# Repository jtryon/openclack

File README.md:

# OpenClack.TKL

## Preface
This repository contains all the source files needed to create a 87 key (tenkeyless) mechanical keyboard.</br>
In order to actually build this keep in mind you'll need access to the following.
* PCB fabrication.
* CNC, laser or waterjet cutting.
* Soldering iron and supplies.
* A source for your switches, stabilizers and electronic components.

## Licensing
Software in this project is licensed under the GPL.  See GPL.md</br>
Hardware in this project is licensed under the TAPR.  See TAPR.md

## Details
* Tenkeyless layout.
* Compatible with Cherry MX switches and both Cherry and Costar stabilizers.
* LED support for each key.
* Does not require a resistor for each LED.
* N-Key roll-over, no ghosting, 1 diode per switch.
* Firmware which allows for custom key mapping, macros, de-bouncing and LED control.
* Mini-B connector.
* Teensy 2.0++ controller.
Some images of a completed prototype based on the designs in this repo are in the "prototype_images" folder.

## Project Files
* /dashkey/* - Firmware for the keyboard, codenamed DashKey.  Coded by SiberX.
* /fabrication/* - Final project files to be sent off and fabricated.
* /kicad_files/* - Kicad project.  Open the file "openclack-tkl.pro".
* /notes/* - Notes explaining the LED configuration, parts list, info on the boost converter, resistors.
* openclack.skp - Rough 3D render of the project (SketchUp).

## Instructions
There's currently no guide on how to do this but if you're technically inclined it should be doable with all the files contained herein.  If someone wants to develop a guide feel free to contribute!

## Loading Firmware
WIP

## Sources/Thanks
Thanks to the folks at http://deskthority.net/ for helping out when I had questions about measurements!</br>
Also a big thanks to BathroomEpiphanies.  Wouldn't have been able to do it without your amazing wiki.  [Check it out here!](http://deskthority.net/wiki/KiCAD_keyboard_PCB_design_guide)

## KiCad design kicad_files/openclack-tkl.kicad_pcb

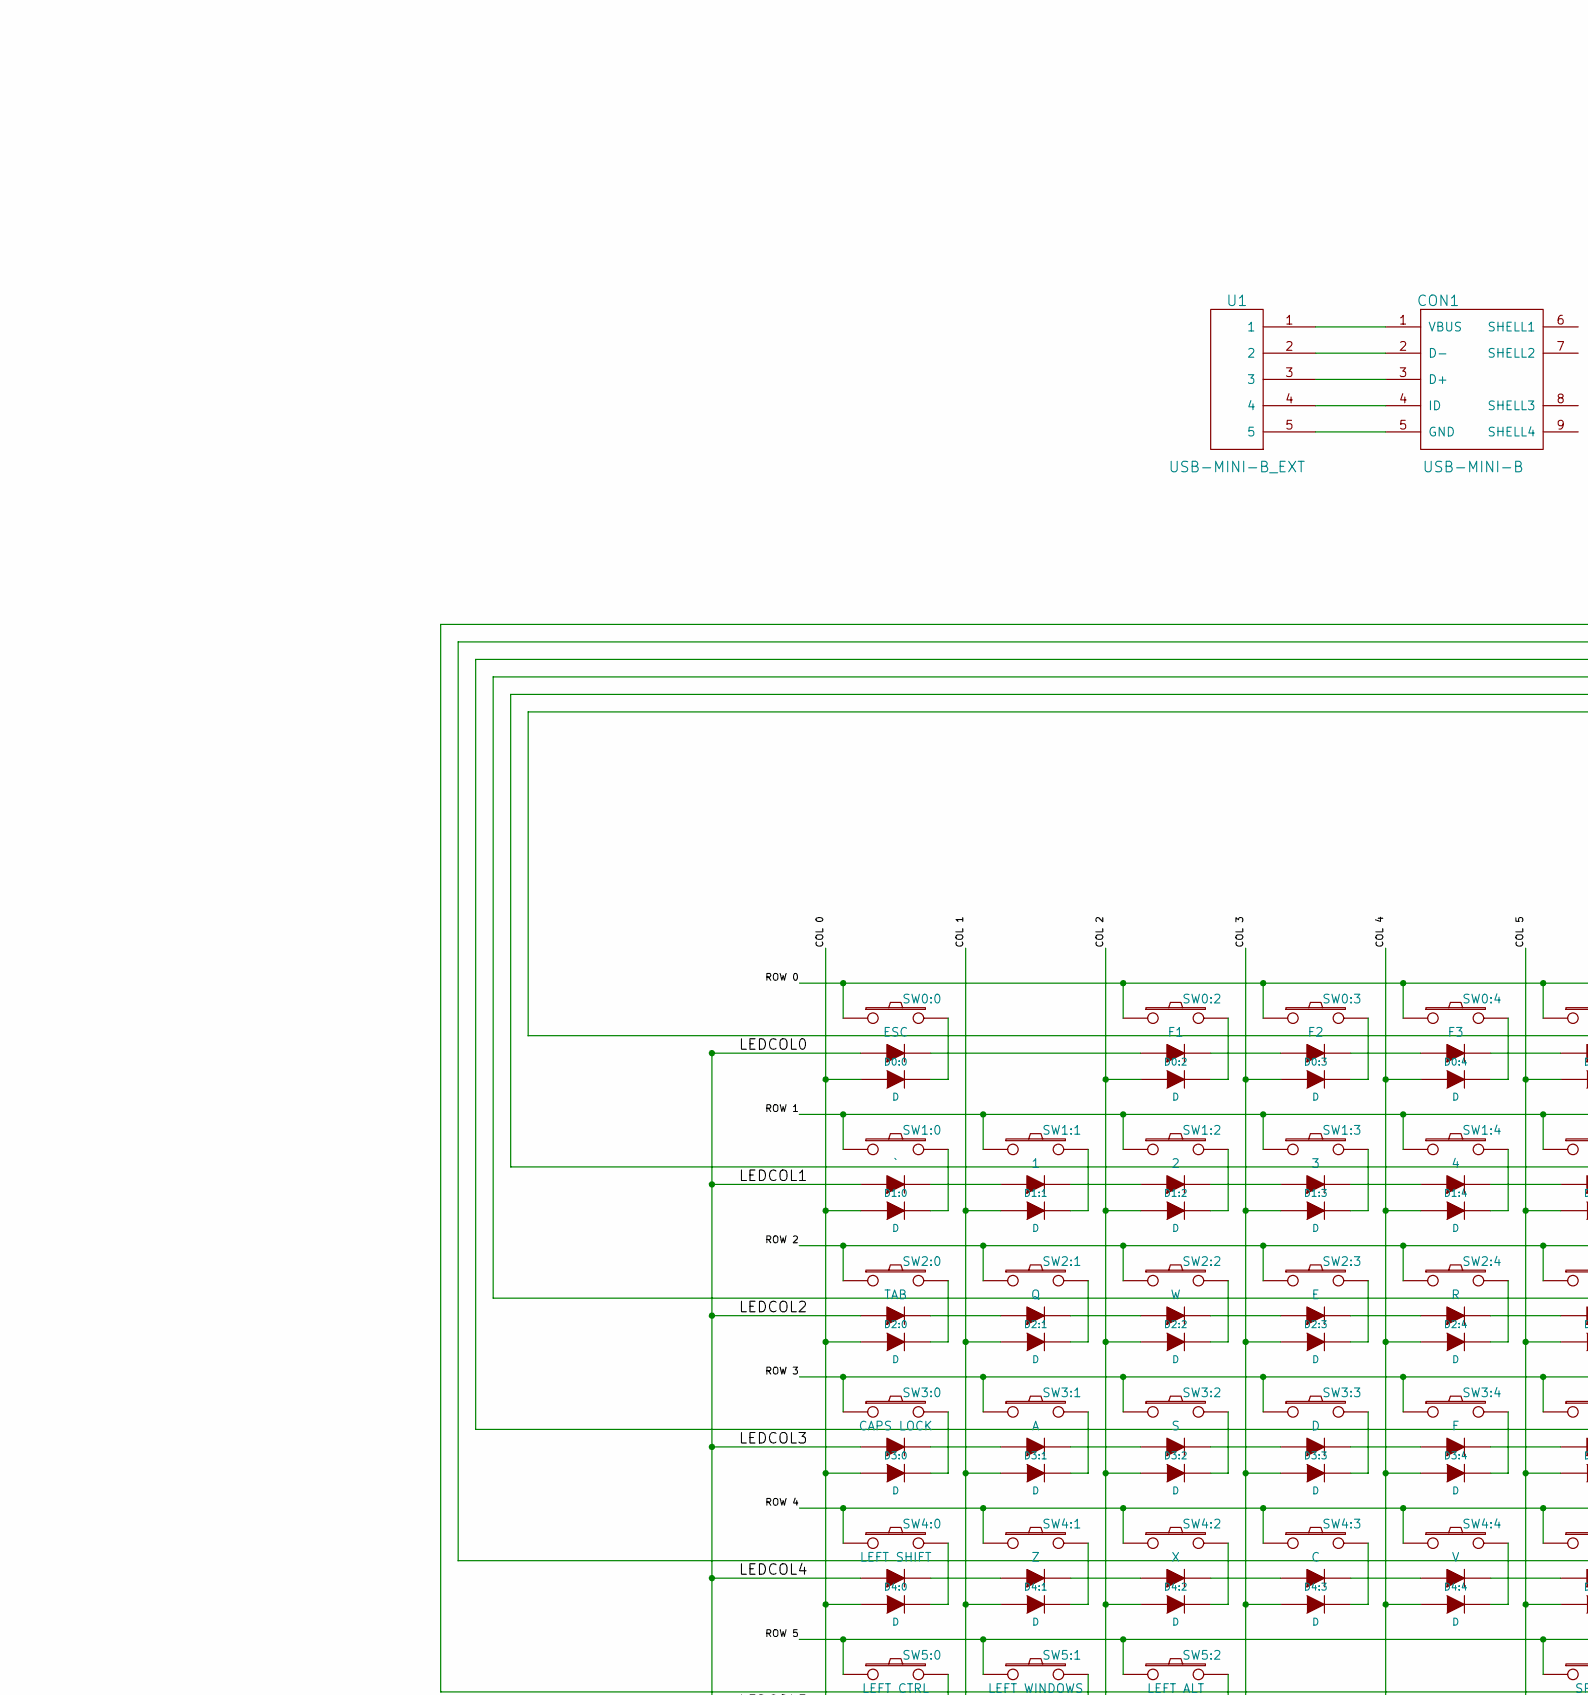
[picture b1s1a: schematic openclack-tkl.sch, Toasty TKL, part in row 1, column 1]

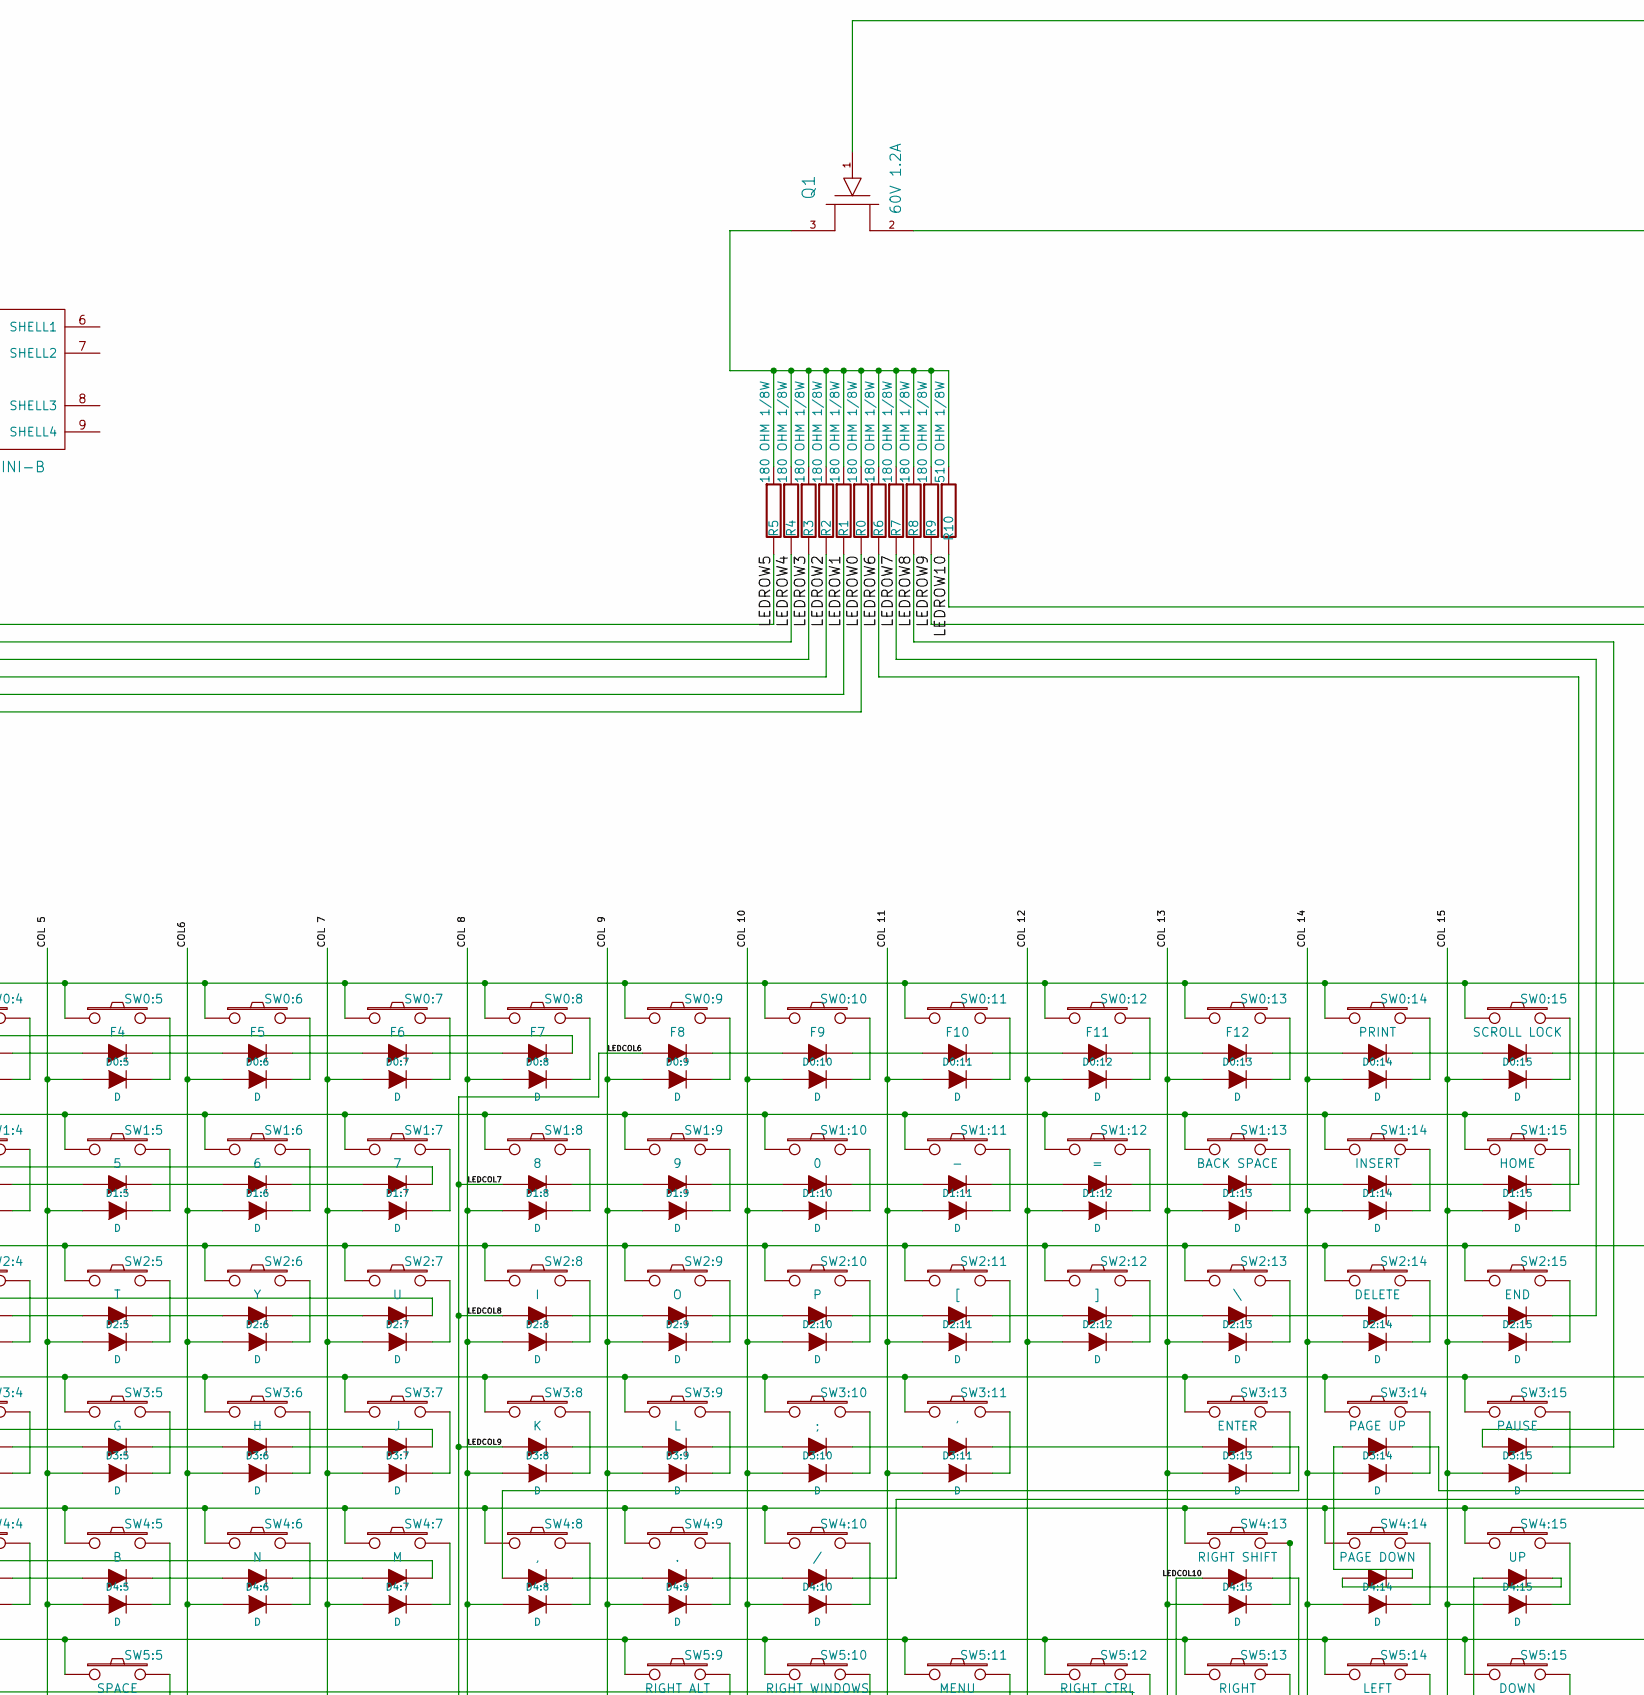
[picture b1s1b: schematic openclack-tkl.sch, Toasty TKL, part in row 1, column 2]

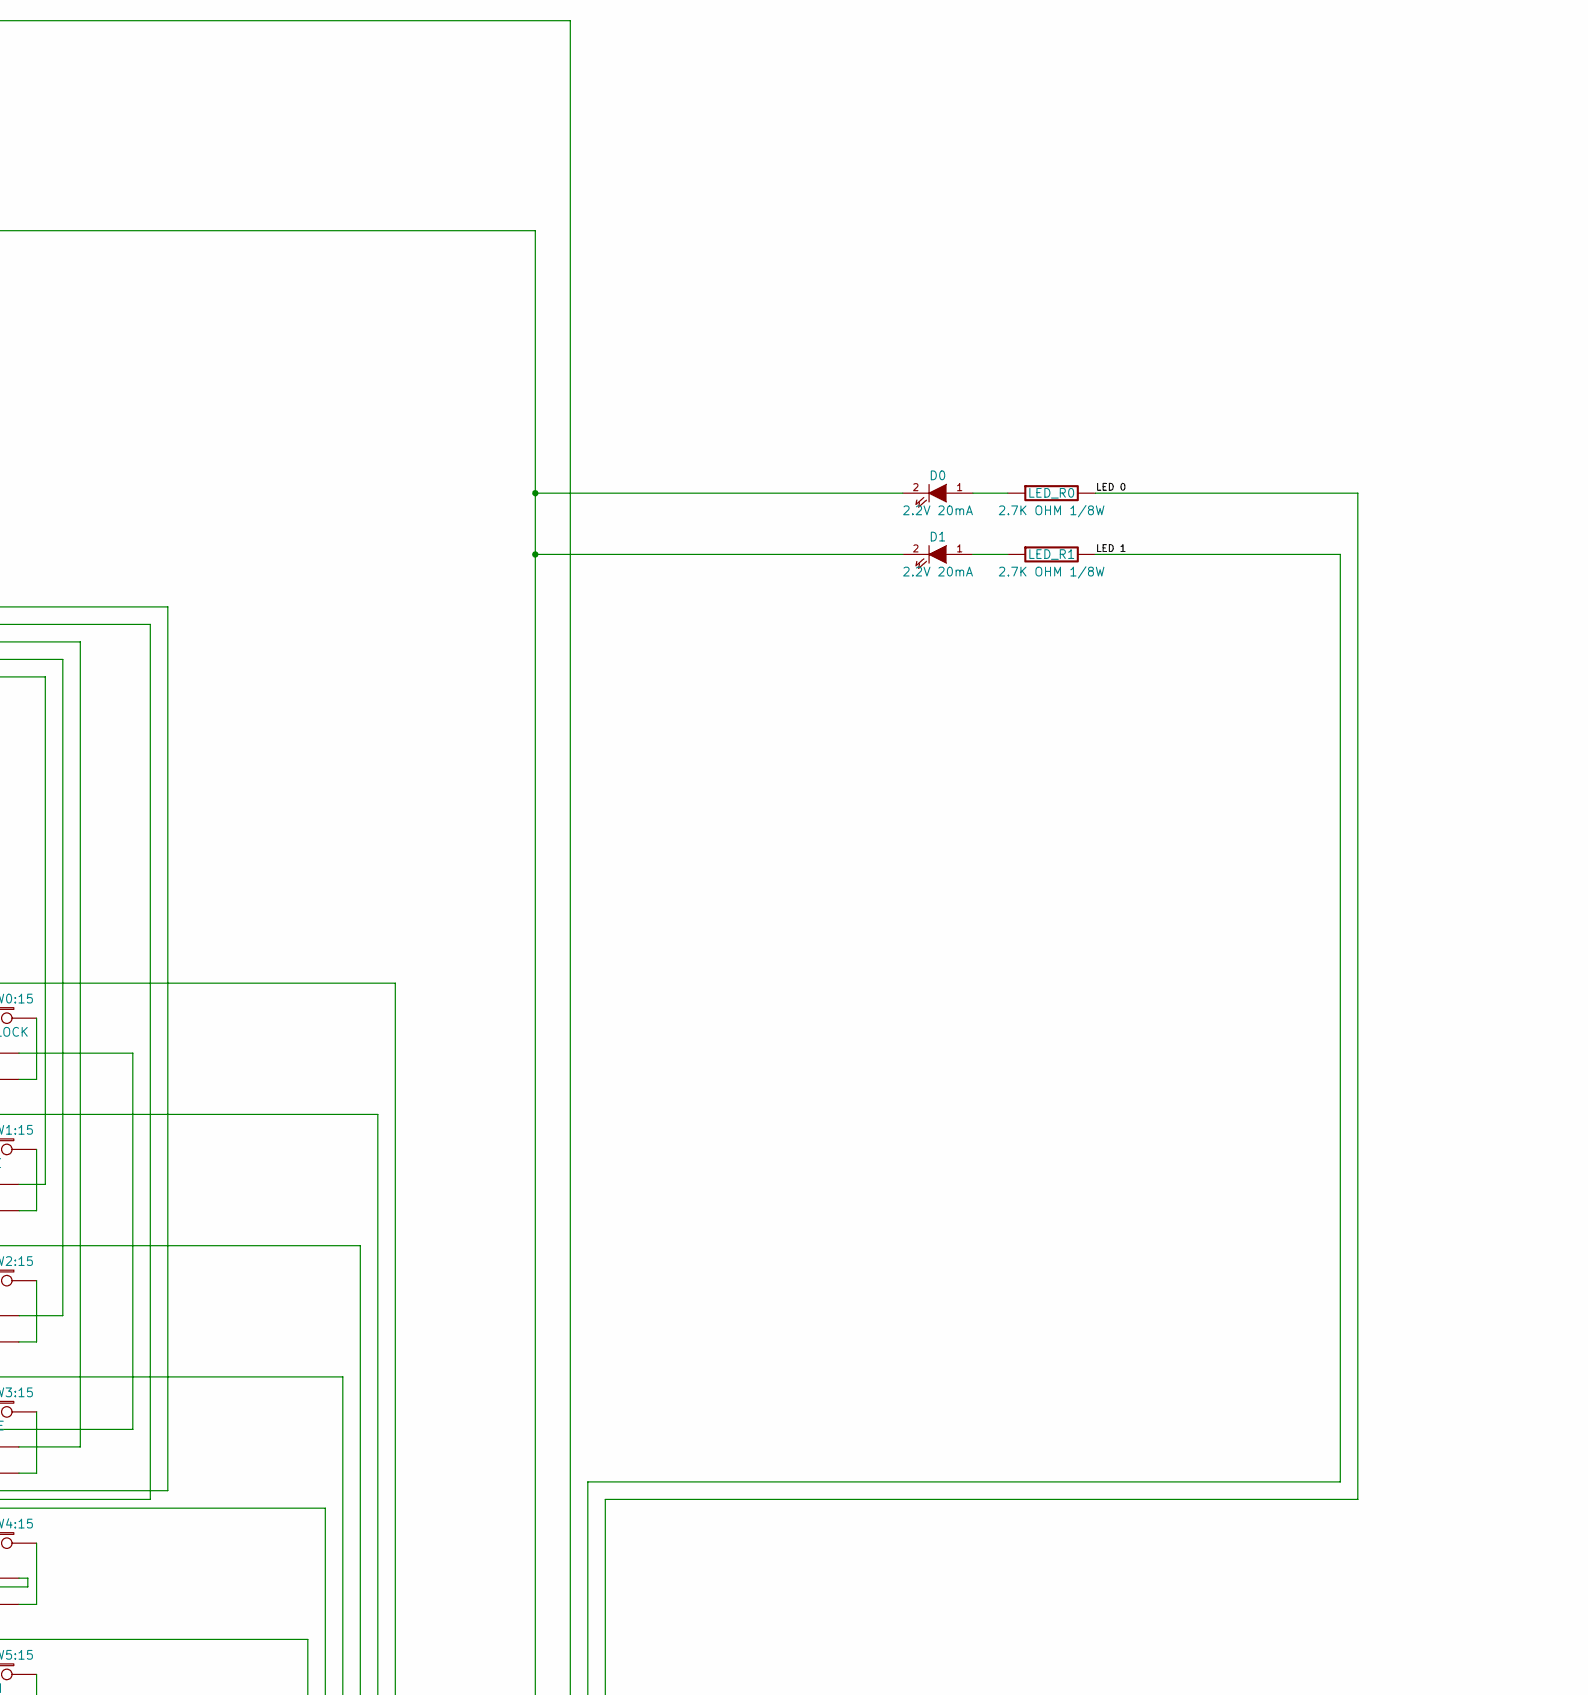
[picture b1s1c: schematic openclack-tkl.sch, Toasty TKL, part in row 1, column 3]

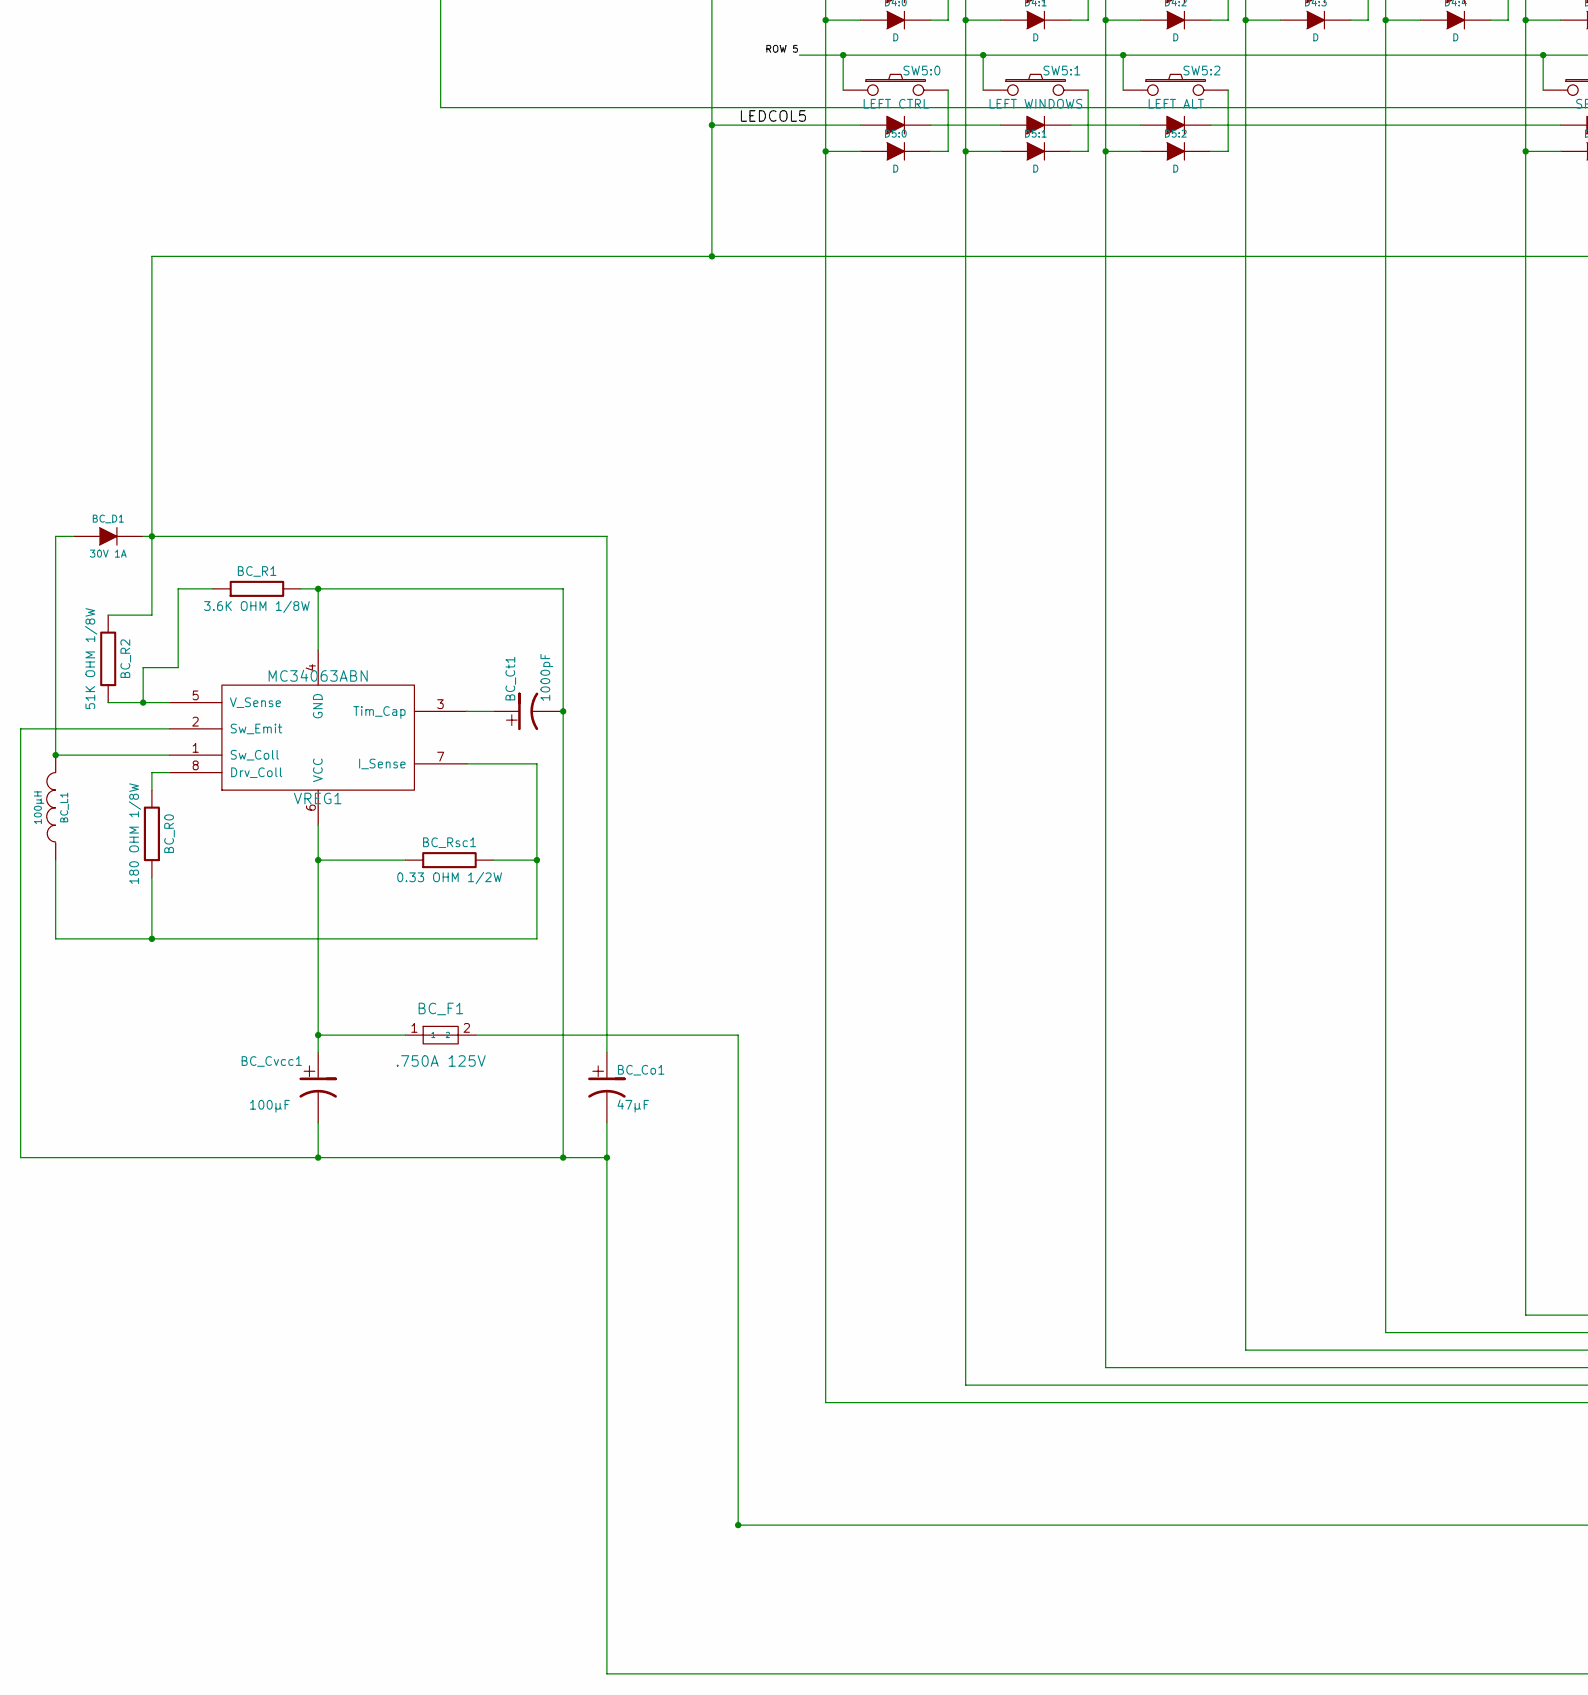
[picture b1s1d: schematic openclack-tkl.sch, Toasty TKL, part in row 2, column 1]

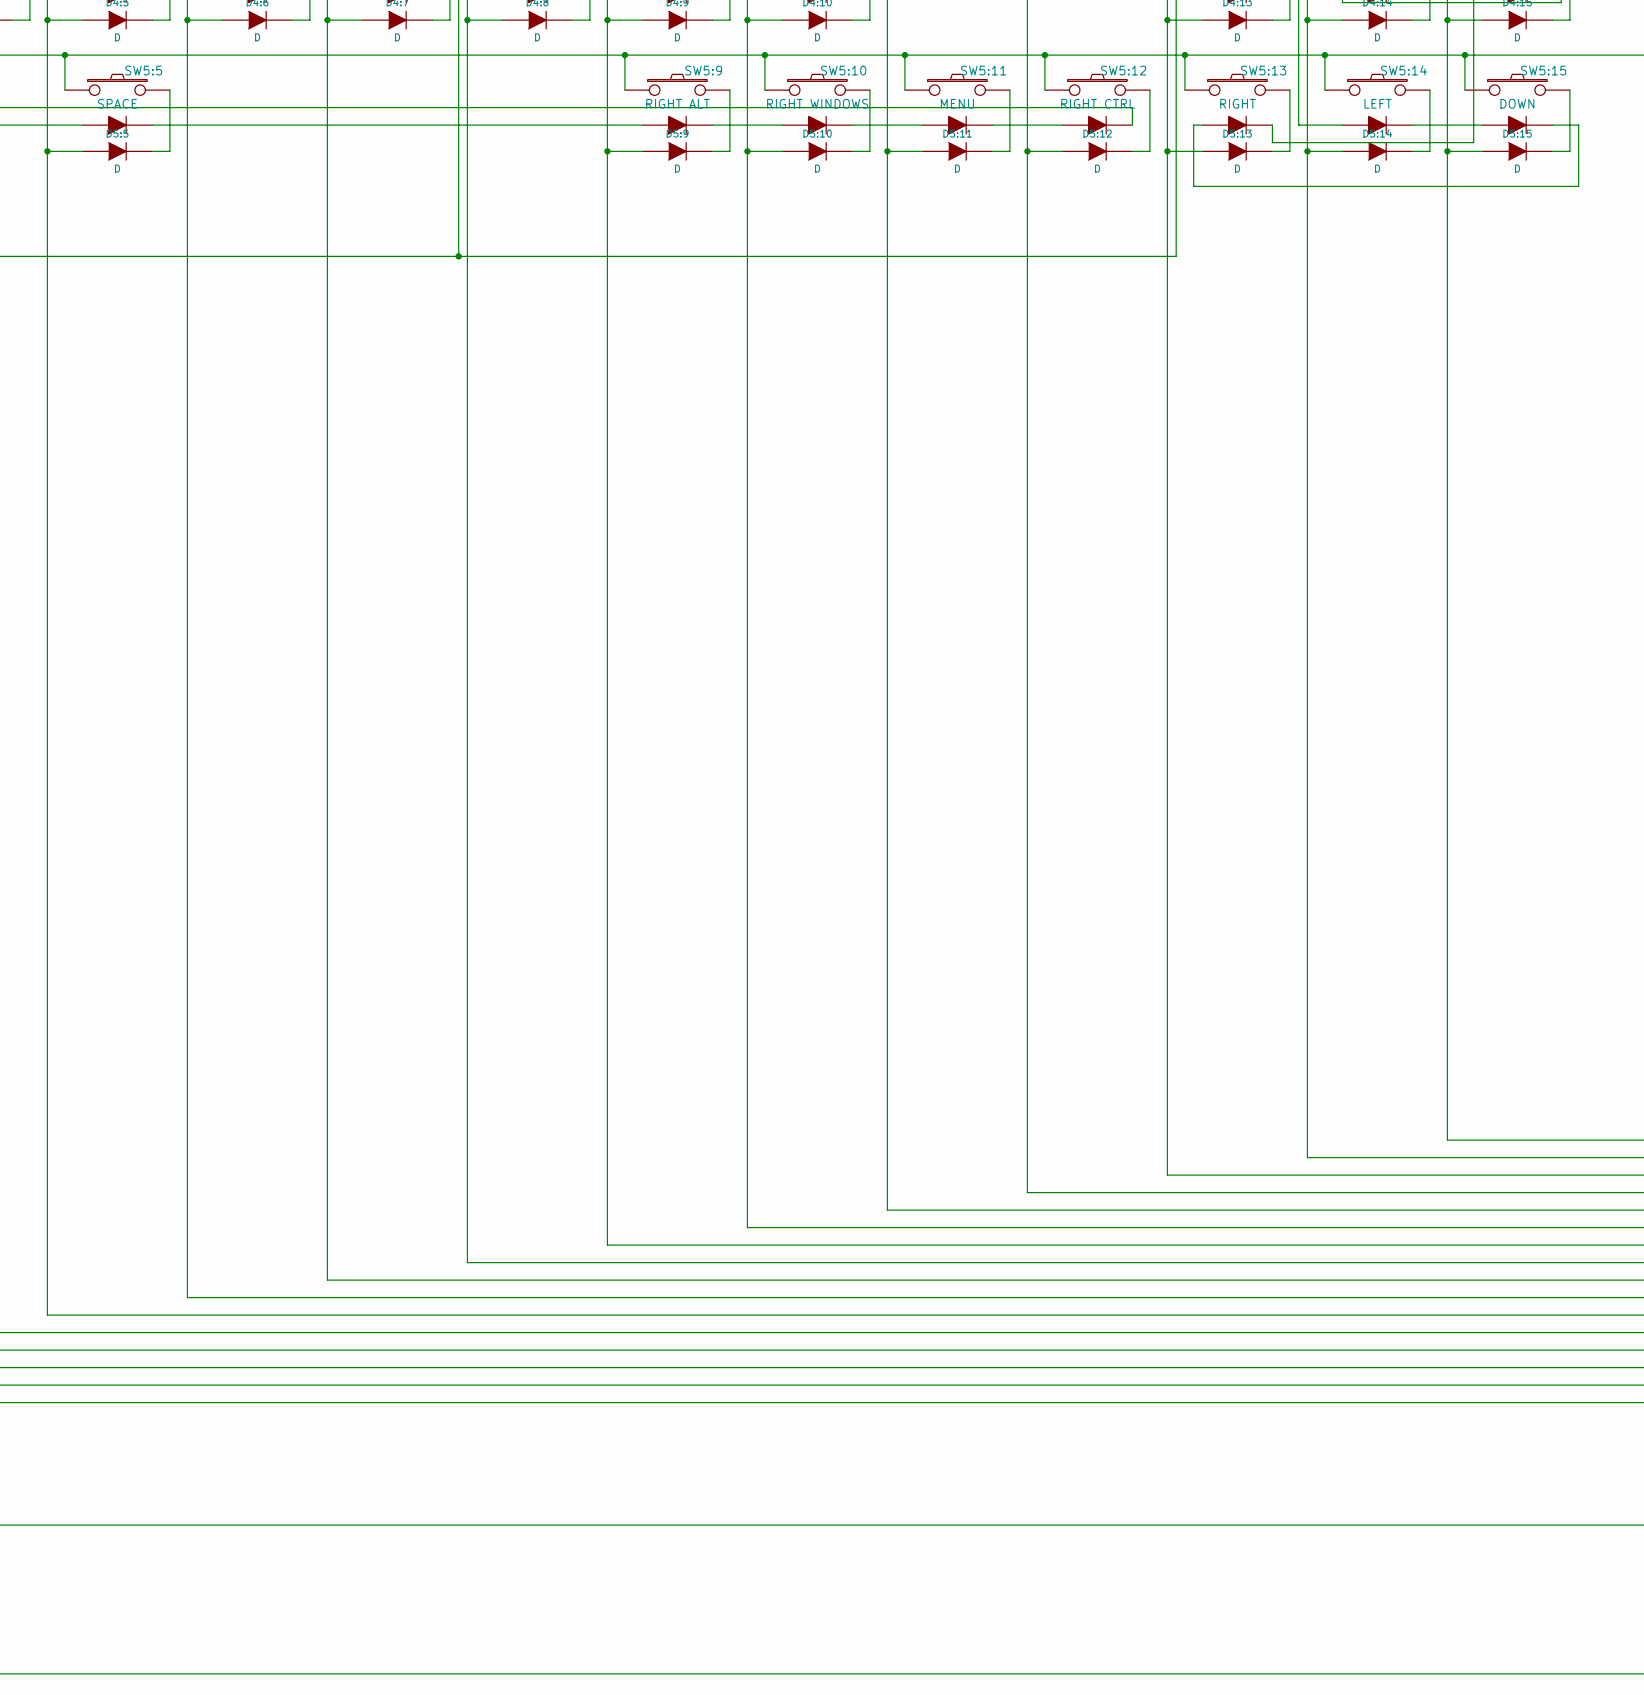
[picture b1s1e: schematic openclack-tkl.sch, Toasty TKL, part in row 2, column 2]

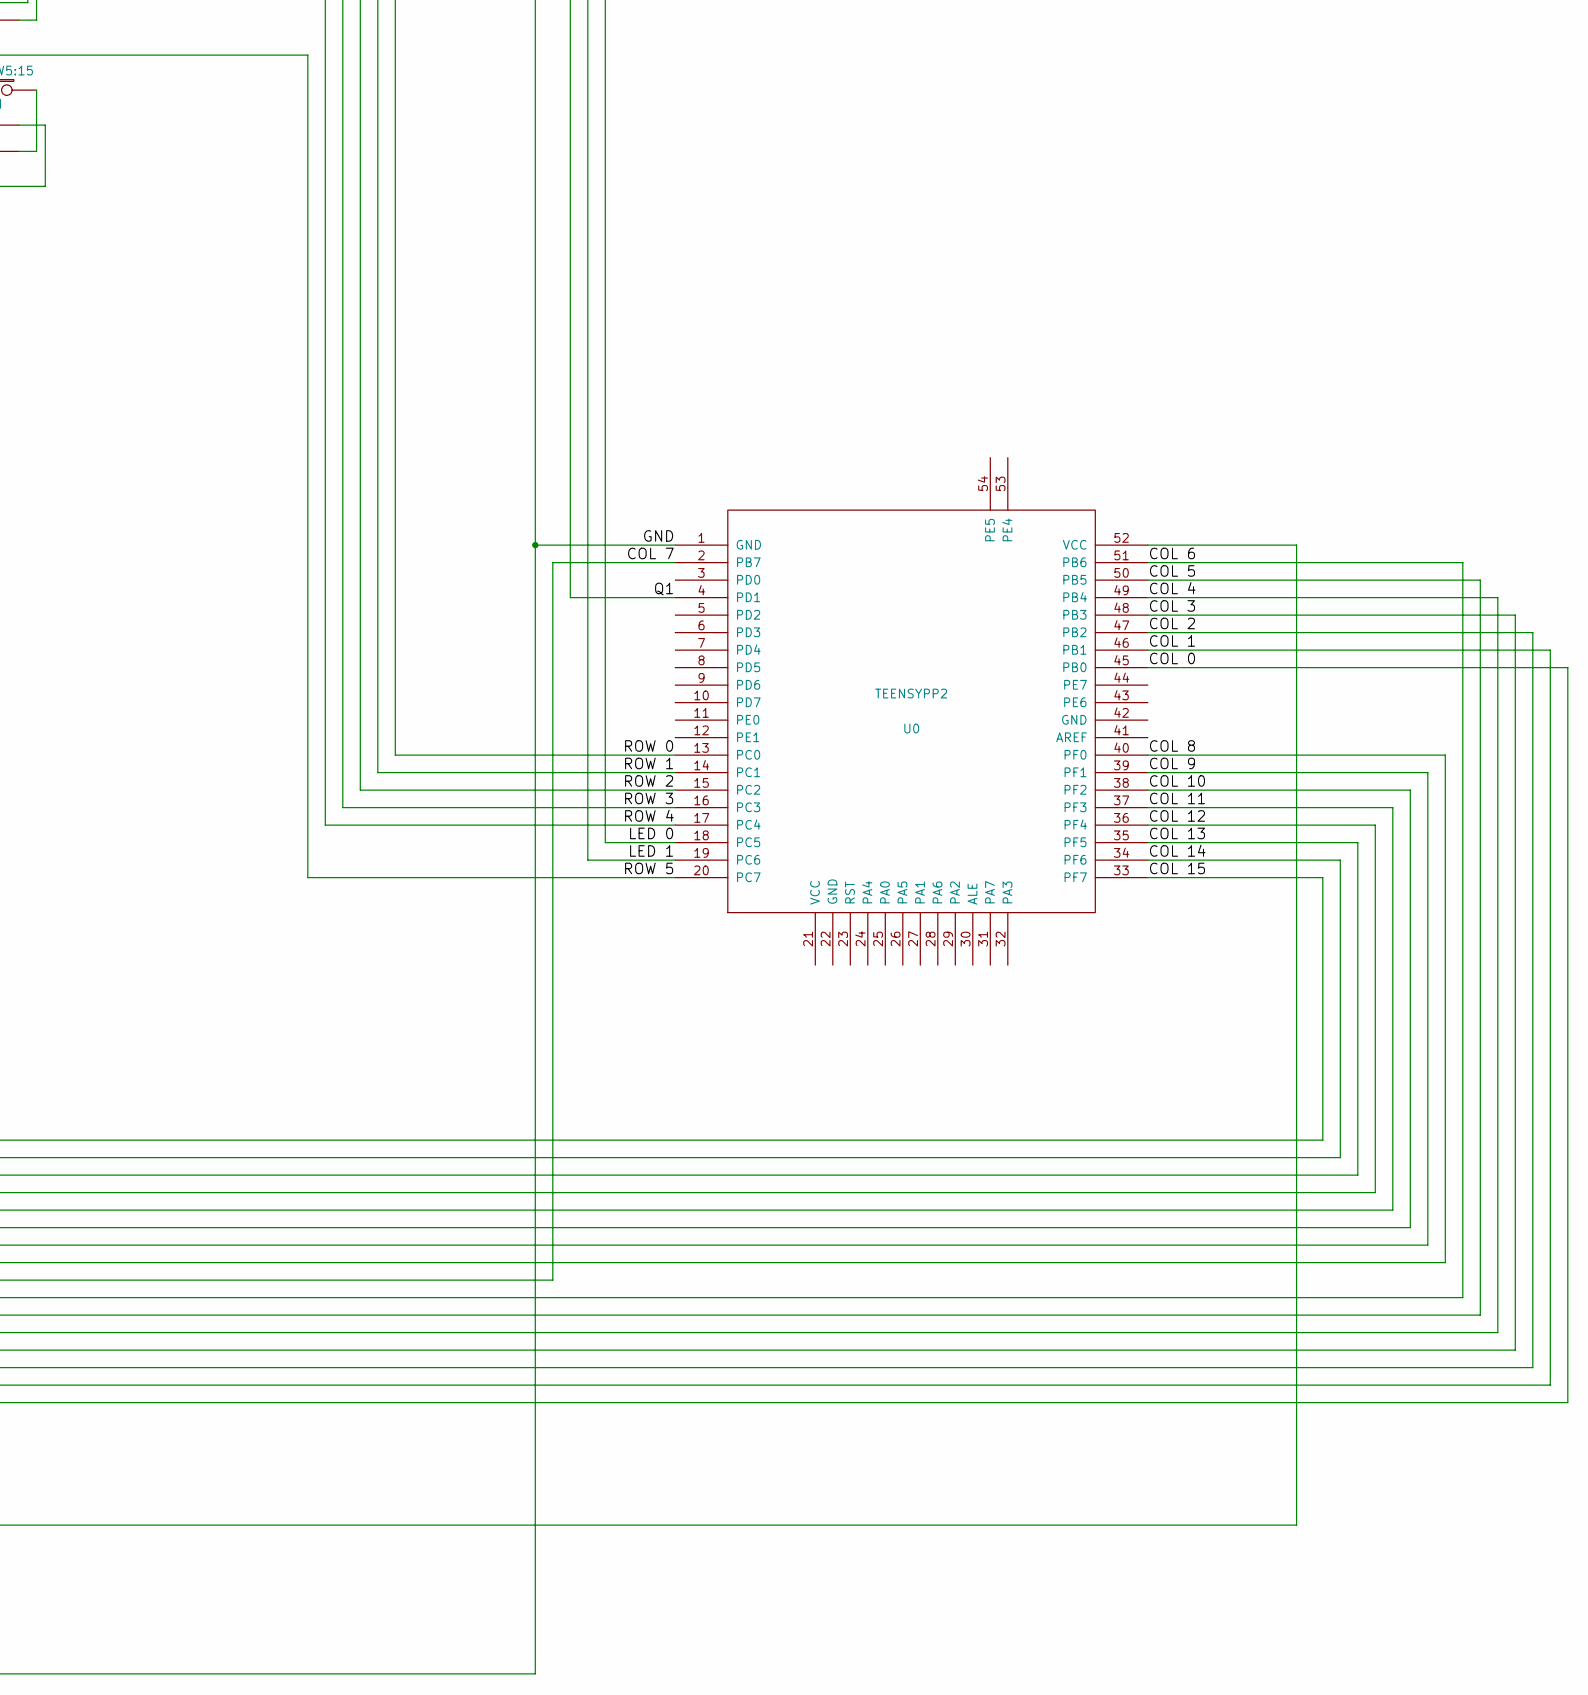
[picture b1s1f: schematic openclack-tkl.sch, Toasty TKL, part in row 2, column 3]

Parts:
BC_Co1: 47µF
BC_Ct1: 1000pF
BC_Cvcc1: 100µF
BC_D1: 30V 1A
BC_F1: .750A 125V
BC_L1: 100µH
BC_R0: 180 OHM 1/8W
BC_R1: 3.6K OHM 1/8W
BC_R2: 51K OHM 1/8W
BC_Rsc1: 0.33 OHM 1/2W
CON1: USB-MINI-B
D0, D1: 2.2V 20mA
D0:0, D0:2, D0:3, D0:4, D0:5, D0:6, D0:7, D0:8, D0:9, D0:10, D0:11, D0:12, D0:13, D0:14, D0:15, D1:0, D1:1, D1:2, D1:3, D1:4, D1:5, D1:6, D1:7, D1:8, D1:9, D1:10, D1:11, D1:12, D1:13, D1:14, D1:15, D2:0, D2:1, D2:2, D2:3, D2:4, D2:5, D2:6, D2:7, D2:8, D2:9, D2:10, D2:11, D2:12, D2:13, D2:14, D2:15, D3:0, D3:1, D3:2, D3:3, D3:4, D3:5, D3:6, D3:7, D3:8, D3:9, D3:10, D3:11, D3:13, D3:14, D3:15, D4:0, D4:1, D4:2, D4:3, D4:4, D4:5, D4:6, D4:7, D4:8, D4:9, D4:10, D4:13, D4:14, D4:15, D5:0, D5:1, D5:2, D5:5, D5:9, D5:10, D5:11, D5:12, D5:13, D5:14, D5:15: D
LED_R0, LED_R1: 2.7K OHM 1/8W
Q1: 60V 1.2A
R0, R1, R2, R3, R4, R5, R6, R7, R8, R9: 180 OHM 1/8W
R10: 510 OHM 1/8W
SW0:0: ESC
SW0:2: F1
SW0:3: F2
SW0:4: F3
SW0:5: F4
SW0:6: F5
SW0:7: F6
SW0:8: F7
SW0:9: F8
SW0:10: F9
SW0:11: F10
SW0:12: F11
SW0:13: F12
SW0:14: PRINT
SW0:15: SCROLL LOCK
SW1:0: `
SW1:1: 1
SW1:2: 2
SW1:3: 3
SW1:4: 4
SW1:5: 5
SW1:6: 6
SW1:7: 7
SW1:8: 8
SW1:9: 9
SW1:10: 0
SW1:11: -
SW1:12: =
SW1:13: BACK SPACE
SW1:14: INSERT
SW1:15: HOME
SW2:0: TAB
SW2:1: Q
SW2:2: W
SW2:3: E
SW2:4: R
SW2:5: T
SW2:6: Y
SW2:7: U
SW2:8: I
SW2:9: O
SW2:10: P
SW2:11: [
SW2:12: ]
SW2:13: \\
SW2:14: DELETE
SW2:15: END
SW3:0: CAPS LOCK
SW3:1: A
SW3:2: S
SW3:3: D
SW3:4: F
SW3:5: G
SW3:6: H
SW3:7: J
SW3:8: K
SW3:9: L
SW3:10: ;
SW3:11: '
SW3:13: ENTER
SW3:14: PAGE UP
SW3:15: PAUSE
SW4:0: LEFT SHIFT
SW4:1: Z
SW4:2: X
SW4:3: C
SW4:4: V
SW4:5: B
SW4:6: N
SW4:7: M
SW4:8: ,
SW4:9: .
SW4:10: /
SW4:13: RIGHT SHIFT
SW4:14: PAGE DOWN
SW4:15: UP
SW5:0: LEFT CTRL
SW5:1: LEFT WINDOWS
SW5:2: LEFT ALT
SW5:5: SPACE
SW5:9: RIGHT ALT
SW5:10: RIGHT WINDOWS
SW5:11: MENU
SW5:12: RIGHT CTRL
SW5:13: RIGHT
SW5:14: LEFT
SW5:15: DOWN
U0: TEENSYPP2; MODULE
U1: USB-MINI-B_EXT
VREG1: MC34063ABN

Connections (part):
/COL 0: D0:0.1 (A), D1:0.1 (A), D2:0.1 (A), D3:0.1 (A), D4:0.1 (A), D5:0.1 (A), U0.45 (PB0)
/COL 1: D1:1.1 (A), D2:1.1 (A), D3:1.1 (A), D4:1.1 (A), D5:1.1 (A), U0.46 (PB1)
/COL 2: D0:2.1 (A), D1:2.1 (A), D2:2.1 (A), D3:2.1 (A), D4:2.1 (A), D5:2.1 (A), U0.47 (PB2)
/COL 3: D0:3.1 (A), D1:3.1 (A), D2:3.1 (A), D3:3.1 (A), D4:3.1 (A), U0.48 (PB3)
/COL 4: D0:4.1 (A), D1:4.1 (A), D2:4.1 (A), D3:4.1 (A), D4:4.1 (A), U0.49 (PB4)
/COL 5: D0:5.1 (A), D1:5.1 (A), D2:5.1 (A), D3:5.1 (A), D4:5.1 (A), D5:5.1 (A), U0.50 (PB5)
/COL 6: D0:6.1 (A), D1:6.1 (A), D2:6.1 (A), D3:6.1 (A), D4:6.1 (A), U0.51 (PB6)
/COL 7: D0:7.1 (A), D1:7.1 (A), D2:7.1 (A), D3:7.1 (A), D4:7.1 (A), U0.2 (PB7)
/COL 8: D0:8.1 (A), D1:8.1 (A), D2:8.1 (A), D3:8.1 (A), D4:8.1 (A), U0.40 (PF0)
/COL 9: D0:9.1 (A), D1:9.1 (A), D2:9.1 (A), D3:9.1 (A), D4:9.1 (A), D5:9.1 (A), U0.39 (PF1)
/COL 10: D0:10.1 (A), D1:10.1 (A), D2:10.1 (A), D3:10.1 (A), D4:10.1 (A), D5:10.1 (A), U0.38 (PF2)
/COL 11: D0:11.1 (A), D1:11.1 (A), D2:11.1 (A), D3:11.1 (A), D5:11.1 (A), U0.37 (PF3)
/COL 12: D0:12.1 (A), D1:12.1 (A), D2:12.1 (A), D5:12.1 (A), U0.36 (PF4)
/COL 13: D0:13.1 (A), D1:13.1 (A), D2:13.1 (A), D3:13.1 (A), D4:13.1 (A), D5:13.1 (A), U0.35 (PF5)
/COL 14: D0:14.1 (A), D1:14.1 (A), D2:14.1 (A), D3:14.1 (A), D4:14.1 (A), D5:14.1 (A), U0.34 (PF6)
/COL 15: D0:15.1 (A), D1:15.1 (A), D2:15.1 (A), D3:15.1 (A), D4:15.1 (A), D5:15.1 (A), U0.33 (PF7)
/GND: BC_Co1.2, BC_Ct1.2, BC_Cvcc1.2, BC_R1.2, D0.2 (K), D1.2 (K), Q1.2 (S), U0.1 (GND), VREG1.2 (Sw_Emit), VREG1.4 (GND)
/LED 0: LED_R0.2, U0.18 (PC5)
/LED 1: LED_R1.2, U0.19 (PC6)
/LEDCOL0: BC_Co1.1, BC_D1.2 (K), BC_R2.2, SW0:0.4, SW0:9.4, SW1:0.4, SW1:8.4, SW2:0.4, SW2:8.4, SW3:0.4, SW3:8.4, SW4:0.4, SW4:13.4, SW5:0.4
/LEDROW0: R0.2, SW0:8.3
/LEDROW1: R1.2, SW1:7.3
/LEDROW2: R2.2, SW2:7.3
/LEDROW3: R3.2, SW3:7.3
/LEDROW4: R4.2, SW4:7.3
/LEDROW5: R5.2, SW5:12.3
/LEDROW6: R6.2, SW1:15.3
/LEDROW7: R7.2, SW2:15.3
/LEDROW8: R8.2, SW3:15.3
/LEDROW9: R9.2, SW4:10.3
/LEDROW10: R10.2, SW3:14.3
/Q1: Q1.1 (G), U0.4 (PD1)
/ROW 0: SW0:0.1, SW0:2.1, SW0:3.1, SW0:4.1, SW0:5.1, SW0:6.1, SW0:7.1, SW0:8.1, SW0:9.1, SW0:10.1, SW0:11.1, SW0:12.1, SW0:13.1, SW0:14.1, SW0:15.1, U0.13 (PC0)
/ROW 1: SW1:0.1, SW1:1.1, SW1:2.1, SW1:3.1, SW1:4.1, SW1:5.1, SW1:6.1, SW1:7.1, SW1:8.1, SW1:9.1, SW1:10.1, SW1:11.1, SW1:12.1, SW1:13.1, SW1:14.1, SW1:15.1, U0.14 (PC1)
/ROW 2: SW2:0.1, SW2:1.1, SW2:2.1, SW2:3.1, SW2:4.1, SW2:5.1, SW2:6.1, SW2:7.1, SW2:8.1, SW2:9.1, SW2:10.1, SW2:11.1, SW2:12.1, SW2:13.1, SW2:14.1, SW2:15.1, U0.15 (PC2)
/ROW 3: SW3:0.1, SW3:1.1, SW3:2.1, SW3:3.1, SW3:4.1, SW3:5.1, SW3:6.1, SW3:7.1, SW3:8.1, SW3:9.1, SW3:10.1, SW3:11.1, SW3:13.1, SW3:14.1, SW3:15.1, U0.16 (PC3)
/ROW 4: SW4:0.1, SW4:1.1, SW4:2.1, SW4:3.1, SW4:4.1, SW4:5.1, SW4:6.1, SW4:7.1, SW4:8.1, SW4:9.1, SW4:10.1, SW4:13.1, SW4:14.1, SW4:15.1, U0.17 (PC4)
/ROW 5: SW5:0.1, SW5:1.1, SW5:2.1, SW5:5.1, SW5:9.1, SW5:10.1, SW5:11.1, SW5:12.1, SW5:13.1, SW5:14.1, SW5:15.1, U0.20 (PC7)
unnamed: D1:7.2 (K), SW1:7.2
unnamed: D2:7.2 (K), SW2:7.2
unnamed: D3:6.2 (K), SW3:6.2
unnamed: D4:6.2 (K), SW4:6.2
unnamed: D2:6.2 (K), SW2:6.2
unnamed: D3:5.2 (K), SW3:5.2
unnamed: D0:8.2 (K), SW0:8.2
unnamed: D4:5.2 (K), SW4:5.2
unnamed: D0:7.2 (K), SW0:7.2
unnamed: D0:9.2 (K), SW0:9.2
unnamed: D1:9.2 (K), SW1:9.2
unnamed: D4:7.2 (K), SW4:7.2
unnamed: D2:9.2 (K), SW2:9.2
unnamed: D3:8.2 (K), SW3:8.2
unnamed: D2:8.2 (K), SW2:8.2
unnamed: D1:8.2 (K), SW1:8.2
unnamed: D3:7.2 (K), SW3:7.2
unnamed: D5:2.2 (K), SW5:2.2
unnamed: D0:4.2 (K), SW0:4.2
unnamed: D1:4.2 (K), SW1:4.2
unnamed: D2:4.2 (K), SW2:4.2
unnamed: D1:3.2 (K), SW1:3.2
unnamed: D2:3.2 (K), SW2:3.2
unnamed: D3:3.2 (K), SW3:3.2
unnamed: D3:2.2 (K), SW3:2.2
unnamed: D4:2.2 (K), SW4:2.2
unnamed: D3:4.2 (K), SW3:4.2
unnamed: D4:4.2 (K), SW4:4.2
unnamed: D2:5.2 (K), SW2:5.2
unnamed: D0:6.2 (K), SW0:6.2
unnamed: D1:6.2 (K), SW1:6.2
unnamed: D0:5.2 (K), SW0:5.2
unnamed: D4:3.2 (K), SW4:3.2
unnamed: D1:5.2 (K), SW1:5.2
unnamed: D3:13.2 (K), SW3:13.2
unnamed: D4:13.2 (K), SW4:13.2
unnamed: D5:12.2 (K), SW5:12.2
unnamed: D0:14.2 (K), SW0:14.2
unnamed: D1:14.2 (K), SW1:14.2
unnamed: D2:14.2 (K), SW2:14.2
unnamed: D5:14.2 (K), SW5:14.2
unnamed: D3:11.2 (K), SW3:11.2
unnamed: D5:11.2 (K), SW5:11.2
unnamed: D0:13.2 (K), SW0:13.2
unnamed: D1:13.2 (K), SW1:13.2
unnamed: D2:13.2 (K), SW2:13.2
unnamed: D4:14.2 (K), SW4:14.2
unnamed: D3:15.2 (K), SW3:15.2
unnamed: D3:14.2 (K), SW3:14.2
unnamed: D5:15.2 (K), SW5:15.2
unnamed: D5:13.2 (K), SW5:13.2
unnamed: D2:0.2 (K), SW2:0.2
unnamed: D0:15.2 (K), SW0:15.2
unnamed: D1:15.2 (K), SW1:15.2
unnamed: D2:15.2 (K), SW2:15.2
unnamed: D4:15.2 (K), SW4:15.2
unnamed: D4:9.2 (K), SW4:9.2
unnamed: D2:10.2 (K), SW2:10.2
unnamed: D3:9.2 (K), SW3:9.2
unnamed: D5:9.2 (K), SW5:9.2
unnamed: D0:11.2 (K), SW0:11.2
unnamed: D0:10.2 (K), SW0:10.2
unnamed: D4:8.2 (K), SW4:8.2
unnamed: D5:5.2 (K), SW5:5.2
unnamed: D1:10.2 (K), SW1:10.2
unnamed: D1:12.2 (K), SW1:12.2
unnamed: D5:10.2 (K), SW5:10.2
unnamed: D0:12.2 (K), SW0:12.2
unnamed: D2:12.2 (K), SW2:12.2
unnamed: D1:11.2 (K), SW1:11.2
unnamed: D2:11.2 (K), SW2:11.2
unnamed: D3:10.2 (K), SW3:10.2
unnamed: D4:10.2 (K), SW4:10.2
unnamed: CON1.5 (GND), U1.5
unnamed: CON1.4 (ID), U1.4
unnamed: CON1.3 (D+), U1.3
unnamed: CON1.2 (D-), U1.2
unnamed: CON1.1 (VBUS), U1.1
unnamed: SW3:14.4, SW4:14.3
unnamed: SW4:14.4, SW4:15.3
unnamed: D0.1 (A), LED_R0.1
unnamed: SW4:15.4, SW5:13.3
unnamed: SW5:13.4, SW5:15.3
unnamed: D1.1 (A), LED_R1.1
unnamed: BC_R1.1, BC_R2.1, VREG1.5 (V_Sense)
unnamed: BC_D1.1 (A), BC_L1.2, VREG1.1 (Sw_Coll)
unnamed: BC_Cvcc1.1, BC_F1.1, BC_Rsc1.1, VREG1.6 (VCC)
unnamed: BC_F1.2, U0.52 (VCC)
unnamed: BC_R0.2, VREG1.8 (Drv_Coll)
unnamed: BC_Ct1.1, VREG1.3 (Tim_Cap)
unnamed: SW2:14.3, SW2:15.4
unnamed: SW4:13.3, SW5:14.4
unnamed: SW3:11.3, SW3:13.4
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
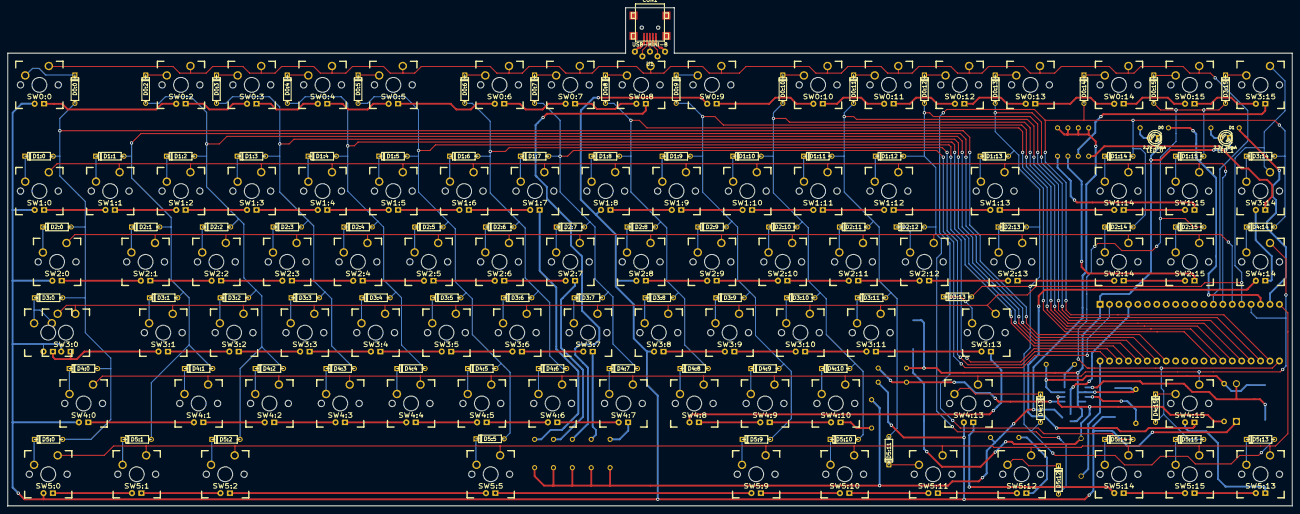
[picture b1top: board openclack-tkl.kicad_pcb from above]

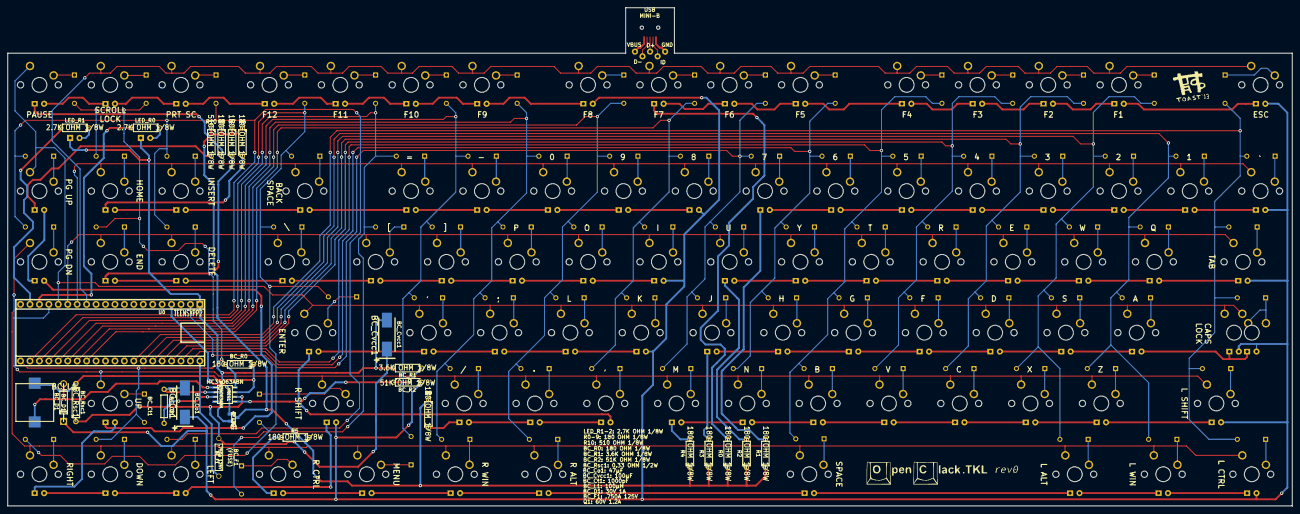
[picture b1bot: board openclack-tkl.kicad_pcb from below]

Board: 2 copper layers, 345.7 x 134.1 mm, 204 parts (26 on the bottom side), 216 nets.
